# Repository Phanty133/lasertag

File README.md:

# lasertag

fun little side project

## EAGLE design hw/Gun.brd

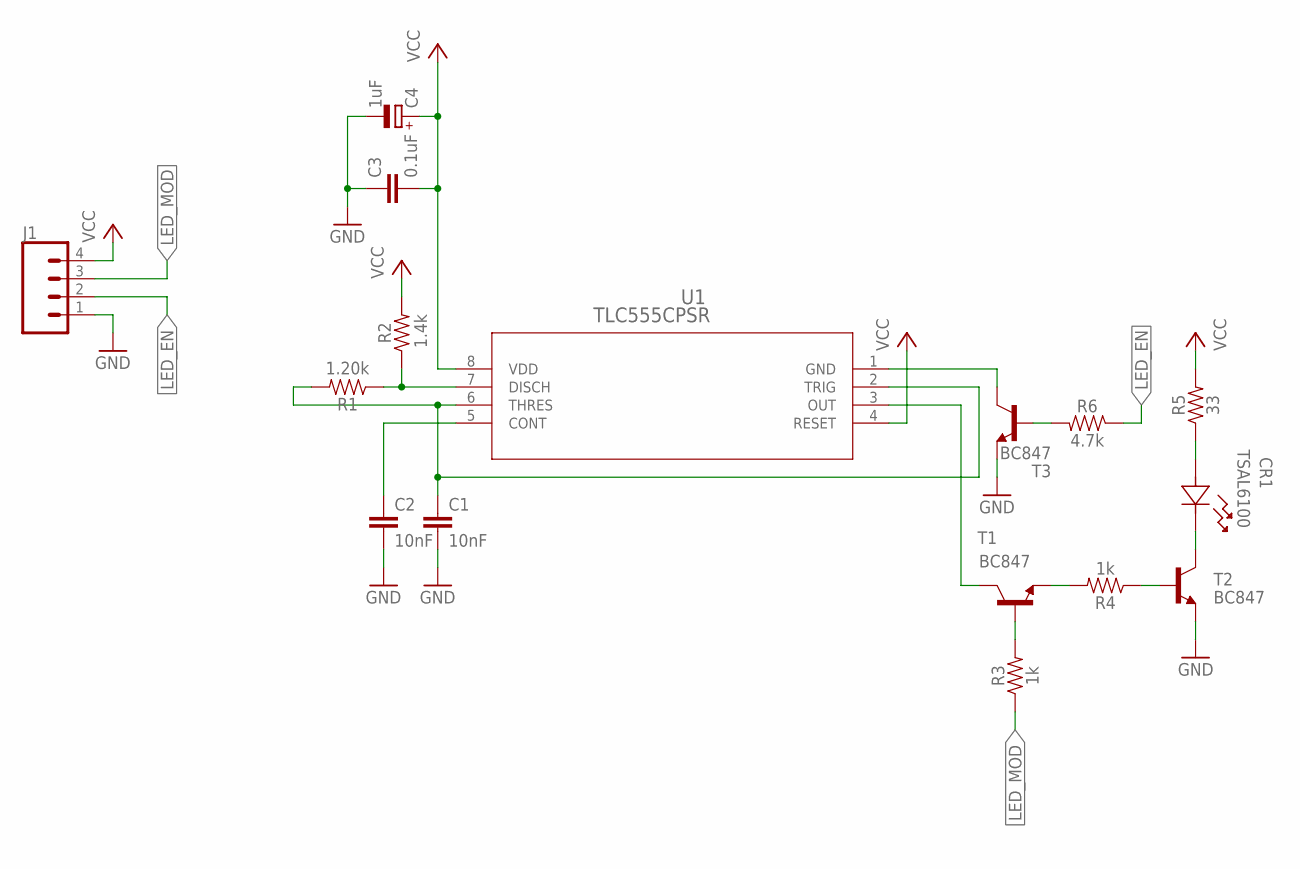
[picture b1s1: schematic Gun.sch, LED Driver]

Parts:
C1, C2: 10nF; 0603
C3: 0.1uF; 0603
C4: 1uF; E2,5-5
CR1: TSAL6100; LED_TLH
J1: CONN_04POLAR; MOLEX-1X4
R1: 1.20k; 0603
R2: 1.4k; 0603
R3, R4: 1k; 0603
R5: 33; 0603
R6: 4.7k; 0603
T1, T2, T3: BC847; SOT23
U1: TLC555CPSR; PS8

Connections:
GND: C1.2, C2.2, C3.1, C4.-, J1.1, T2.2 (E), T3.2 (E)
LED_EN: J1.2, R6.1
LED_MOD: J1.3, R3.1
unnamed: T3.3 (C), U1.1 (GND)
unnamed: R6.2, T3.1 (B)
unnamed: T1.3 (C), U1.3 (OUT)
unnamed: R4.2, T1.2 (E)
unnamed: CR1.1, T2.3 (C)
unnamed: C1.1, R1.2, U1.2 (TRIG), U1.6 (THRES)
unnamed: CR1.2, R5.1
unnamed: R4.1, T2.1 (B)
unnamed: R3.2, T1.1 (B)
unnamed: R1.1, R2.1, U1.7 (DISCH)
unnamed: C2.1, U1.5 (CONT)
VCC: C3.2, C4.+, J1.4, R2.2, R5.2, U1.4 (RESET), U1.8 (VDD)

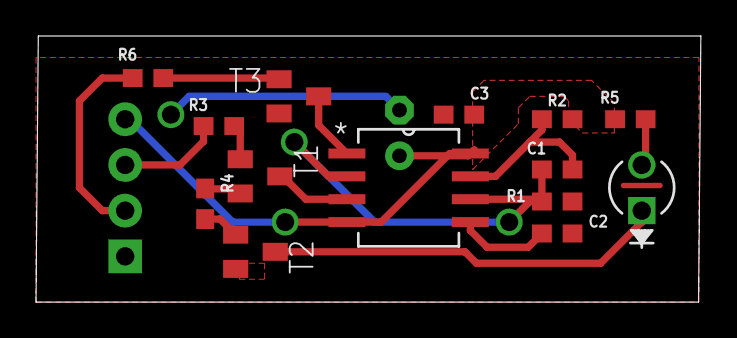
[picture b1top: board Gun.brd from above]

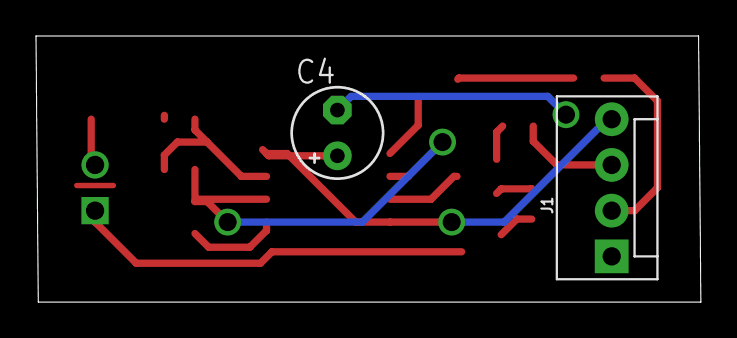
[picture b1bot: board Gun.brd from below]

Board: 2 copper layers, 36.9 x 14.8 mm, 16 parts (2 on the bottom side), 15 nets.

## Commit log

2022-06-14 added existing stuff
2022-06-14 cleanup

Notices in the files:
parts and their libraries:
SparkFun-Capacitors: Licensing: Creative Commons ShareAlike 4.0 International - https://creativecommons.org/licenses/by-sa/4.0
COPYRIGHT: Copyright (C) 2022 Ultra Librarian. All rights reserved.
